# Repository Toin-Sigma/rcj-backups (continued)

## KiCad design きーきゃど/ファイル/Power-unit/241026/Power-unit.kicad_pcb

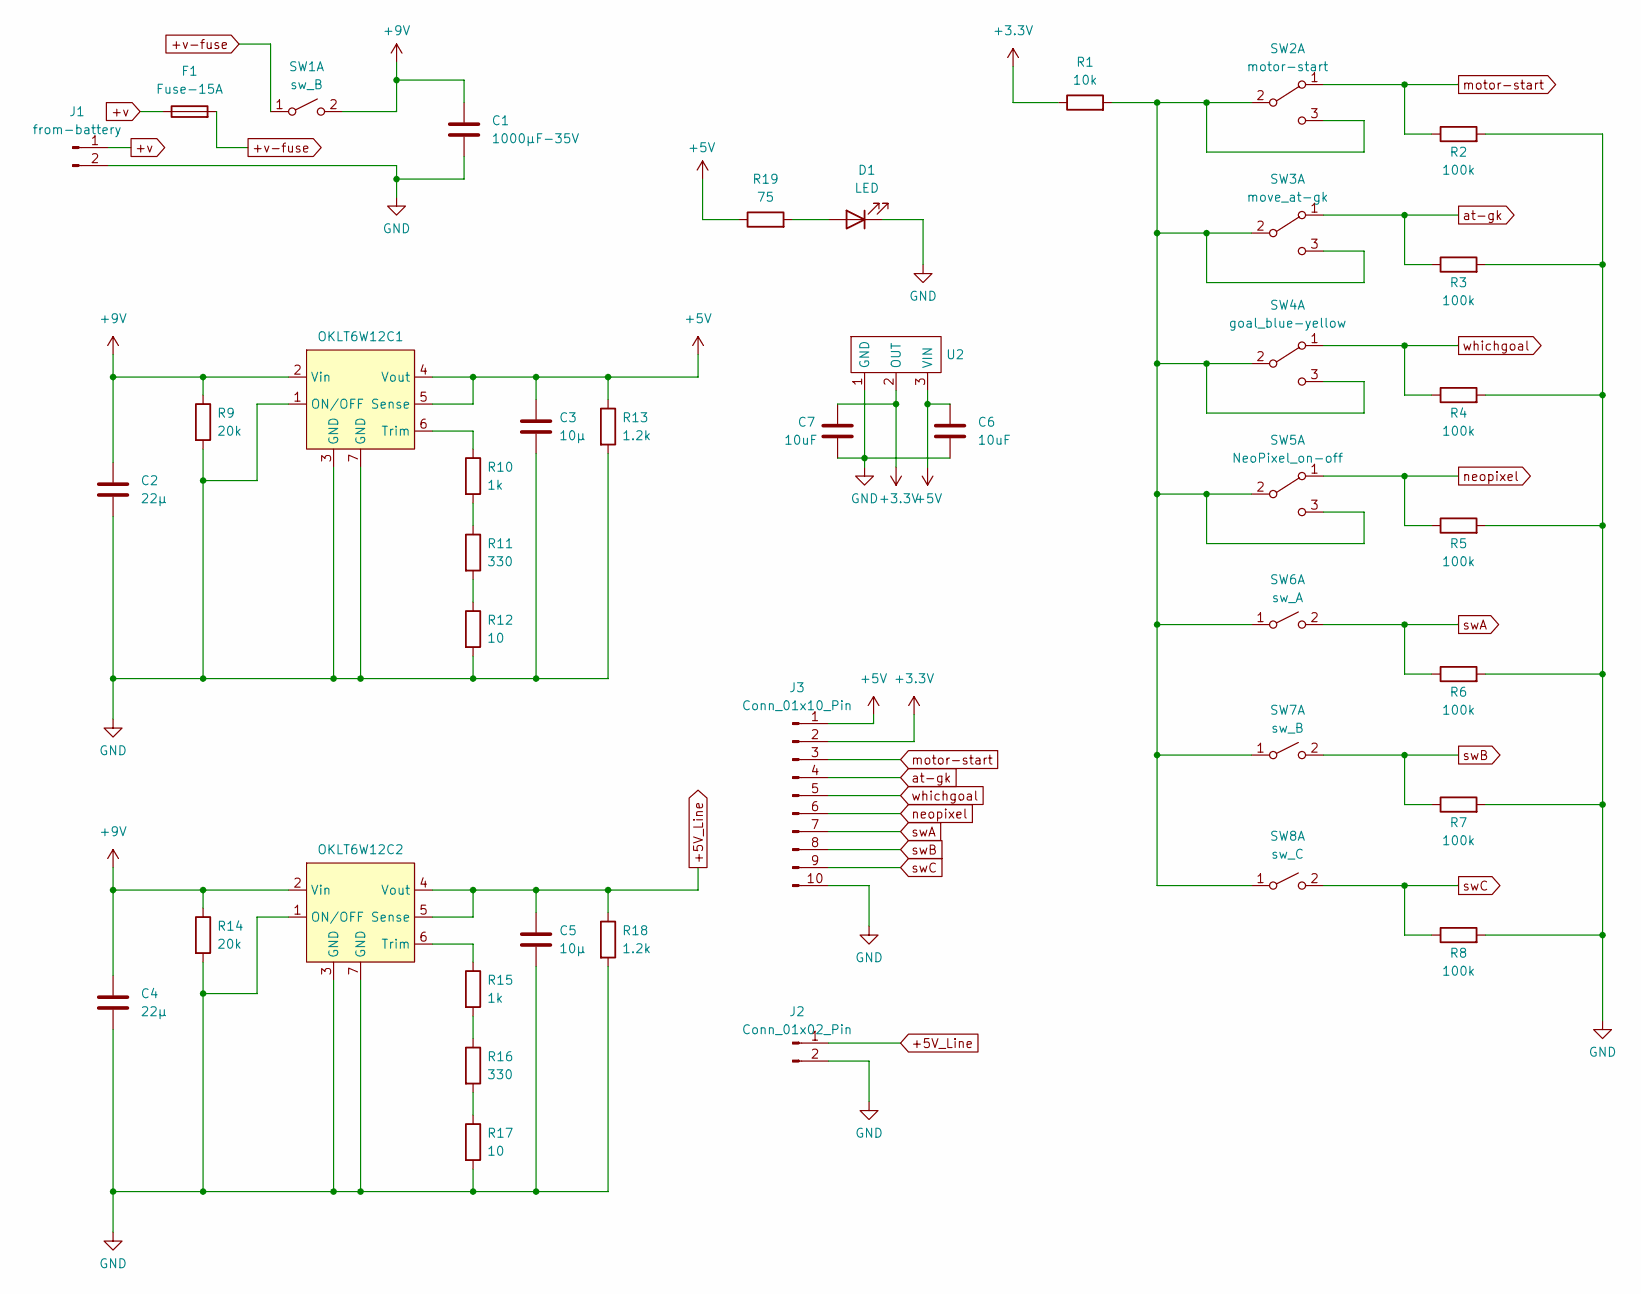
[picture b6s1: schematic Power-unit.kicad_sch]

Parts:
C1: 1000μF-35V; CP_Radial_D12.5mm_P5.00mm
C2, C4: 22μ; C_0805_2012Metric_Pad1.18x1.45mm_HandSolder
C3, C5: 10μ; C_0805_2012Metric_Pad1.18x1.45mm_HandSolder
C6, C7: 10uF; C_0805_2012Metric_Pad1.18x1.45mm_HandSolder
D1: LED; LED_0603_1608Metric
F1: Fuse-15A; mini-fuse-holder
J1: from-battery; vin
J2: Conn_01x02_Pin; AMASS_XT30U-M_1x02_P5.0mm_Vertical
J3: Conn_01x10_Pin; JST_XH_B10B-XH-A_1x10_P2.50mm_Vertical
OKLT6W12C1, OKLT6W12C2: OKL-T6-W12
R1: 10k; R_1206_3216Metric_Pad1.30x1.75mm_HandSolder
R2, R3, R4, R5, R6, R7, R8: 100k; R_1206_3216Metric_Pad1.30x1.75mm_HandSolder
R9, R14: 20k; R_1206_3216Metric_Pad1.30x1.75mm_HandSolder
R10, R15: 1k; R_1206_3216Metric_Pad1.30x1.75mm_HandSolder
R11, R16: 330; R_1206_3216Metric_Pad1.30x1.75mm_HandSolder
R12, R17: 10; R_1206_3216Metric_Pad1.30x1.75mm_HandSolder
R13, R18: 1.2k; R_1206_3216Metric_Pad1.30x1.75mm_HandSolder
R19: 75; R_1206_3216Metric_Pad1.30x1.75mm_HandSolder
SW1: sw_B; 2pin
SW2: motor-start; 2MS1-T1-B4-VS2-Q-E-S
SW3: move_at-gk; 2MS1-T1-B4-VS2-Q-E-S
SW4: goal_blue-yellow; 2MS1-T1-B4-VS2-Q-E-S
SW5: NeoPixel_on-off; 2MS1-T1-B4-VS2-Q-E-S
SW6: sw_A; TVBP06-b043CW-B
SW7: sw_B; TVBP06-b043CW-B
SW8: sw_C; TVBP06-b043CW-B
U2: SOT-223-3_TabPin2

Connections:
+3.3V: C7.2, J3.2, R1.1, U2.2 (OUT); also elsewhere on the board
+5V: C3.1, C6.1, J3.1, OKLT6W12C1.4 (Vout), OKLT6W12C1.5 (Sense), R13.1, R19.1, U2.3 (VIN); also elsewhere on the board
+5V_Line: C5.1, J2.1, OKLT6W12C2.4 (Vout), OKLT6W12C2.5 (Sense), R18.1
+9V: C1.1, C2.1, C4.1, OKLT6W12C1.2 (Vin), OKLT6W12C2.2 (Vin), R9.1, R14.1, SW1.2 (B)
+v: F1.1, J1.1
+v-fuse: F1.2, SW1.1 (A)
GND: C1.2, C2.2, C3.2, C4.2, C5.2, C6.2, C7.1, D1.1 (K), J1.2, J2.2, J3.10, OKLT6W12C1.1 (ON/OFF), OKLT6W12C1.3 (GND), OKLT6W12C1.7 (GND), OKLT6W12C2.1 (ON/OFF), OKLT6W12C2.3 (GND), OKLT6W12C2.7 (GND), R2.2, R3.2, R4.2, R5.2, R6.2, R7.2, R8.2, R9.2, R12.2, R13.2, R14.2, R17.2, R18.2, U2.1 (GND); also elsewhere on the board
unnamed 7: D1.2 (A), R19.2; also elsewhere on the board
unnamed: OKLT6W12C1.6 (Trim), R10.1
unnamed: OKLT6W12C2.6 (Trim), R15.1
unnamed: R10.2, R11.1
unnamed: R11.2, R12.1
unnamed: R15.2, R16.1
unnamed: R16.2, R17.1
unnamed: R1.2, SW2.2 (B), SW2.3 (C), SW3.2 (B), SW3.3 (C), SW4.2 (B), SW4.3 (C), SW5.2 (B), SW5.3 (C), SW6.1 (A), SW7.1 (A), SW8.1 (A)
at-gk: J3.4, R3.1, SW3.1 (A)
motor-start: J3.3, R2.1, SW2.1 (A)
neopixel: J3.6, R5.1, SW5.1 (A)
swA: J3.7, R6.1, SW6.2 (B)
swB: J3.8, R7.1, SW7.2 (B)
swC: J3.9, R8.1, SW8.2 (B)
whichgoal: J3.5, R4.1, SW4.1 (A)

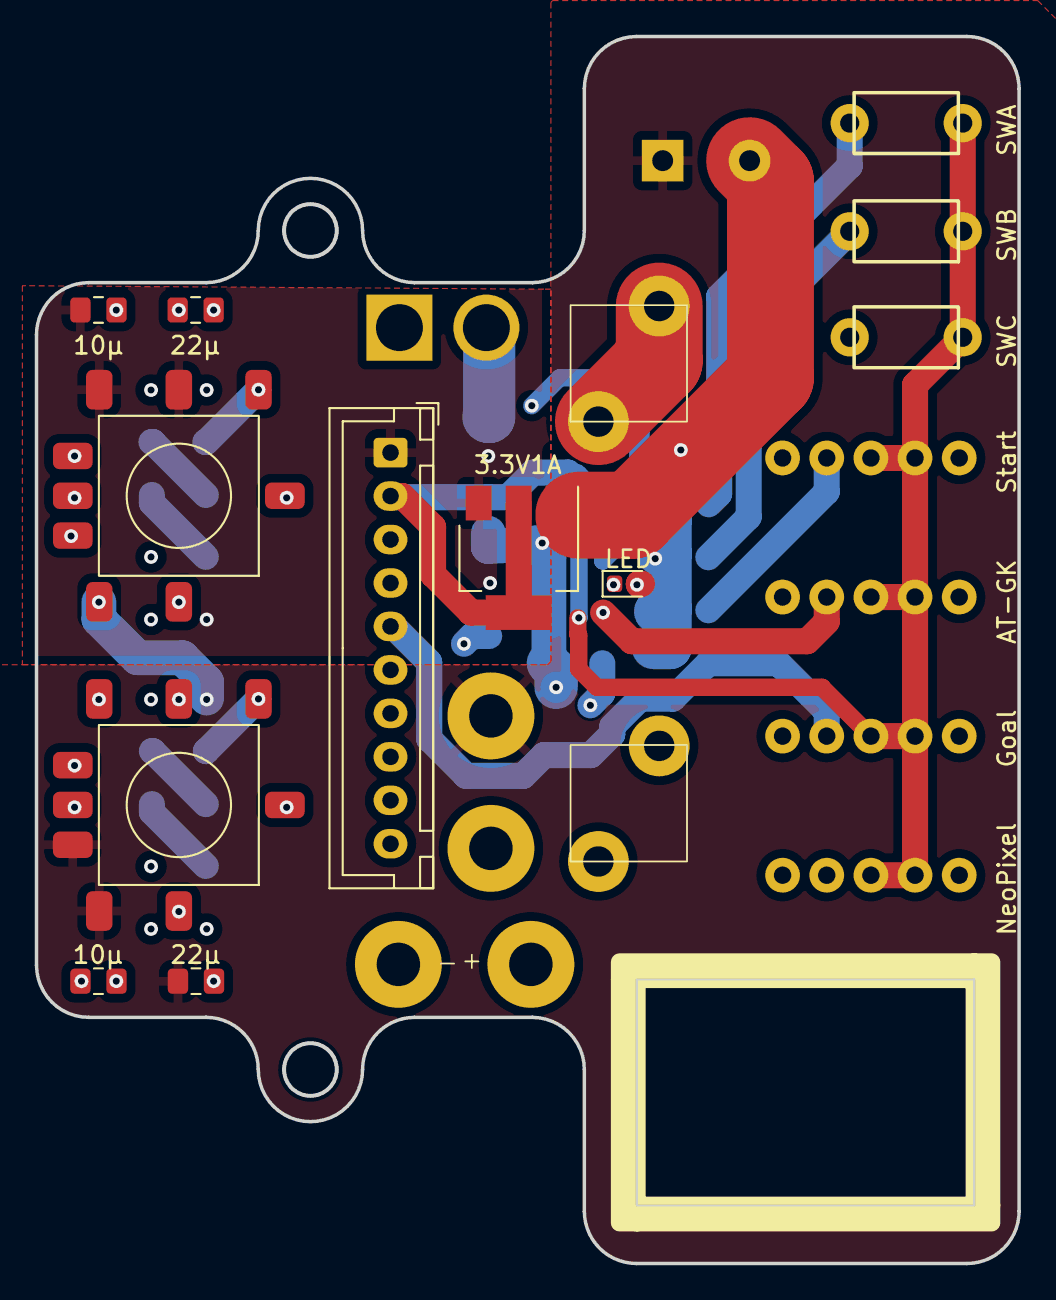
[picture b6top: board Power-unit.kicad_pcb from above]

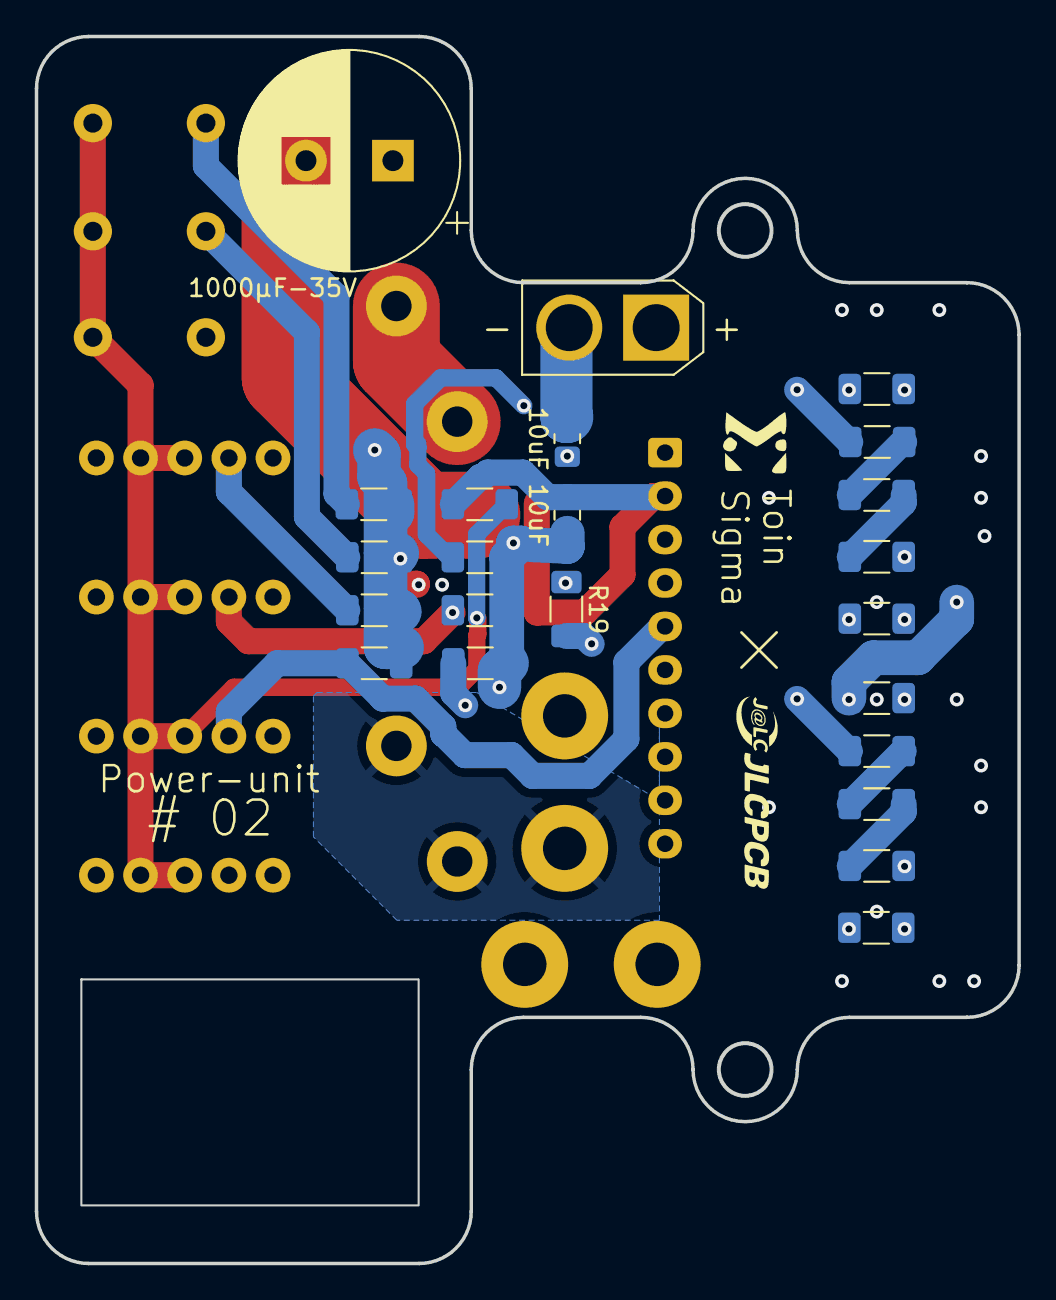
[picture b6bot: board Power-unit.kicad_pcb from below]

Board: 4 copper layers, 56.5 x 70.6 mm, 42 parts (23 on the bottom side), 22 nets.

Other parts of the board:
3.3V1A: SOT-223-3_TabPin2
10uF, 10uF#2: 10uF; C_0805_2012Metric_Pad1.18x1.45mm_HandSolder
LED: LED; LED_0603_1608Metric

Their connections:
+3.3V: 3.3V1A.2 (OUT), 10uF.2; also elsewhere on the board
+5V: 3.3V1A.3 (VIN), 10uF#2.1; also elsewhere on the board
GND: 3.3V1A.1 (GND), 10uF.1, 10uF#2.2, LED.1 (K); also elsewhere on the board
unnamed 7: LED.2 (A); also elsewhere on the board

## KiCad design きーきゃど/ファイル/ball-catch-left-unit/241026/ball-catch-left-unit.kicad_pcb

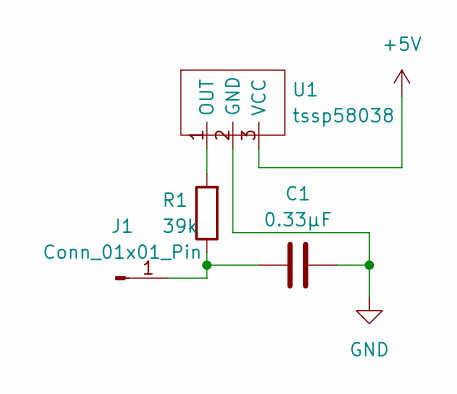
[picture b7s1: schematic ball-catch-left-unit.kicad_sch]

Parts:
C1: 0.33μF; C_0603_1608Metric_Pad1.08x0.95mm_HandSolder
J1: Conn_01x01_Pin; 1-pin
R1: 39k; R_0603_1608Metric_Pad0.98x0.95mm_HandSolder
U1: tssp58038

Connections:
+5V: U1.3 (VCC)
GND: C1.2, U1.2 (GND)
unnamed: C1.1, J1.1, R1.1
unnamed: R1.2, U1.1 (OUT)

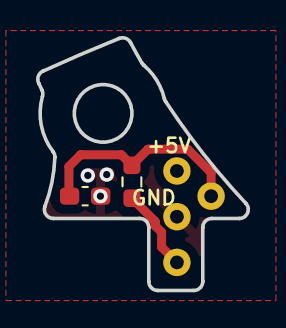
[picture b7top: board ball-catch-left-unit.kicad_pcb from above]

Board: 2 copper layers, 11.7 x 14.0 mm, 4 parts (1 on the bottom side), 3 nets.

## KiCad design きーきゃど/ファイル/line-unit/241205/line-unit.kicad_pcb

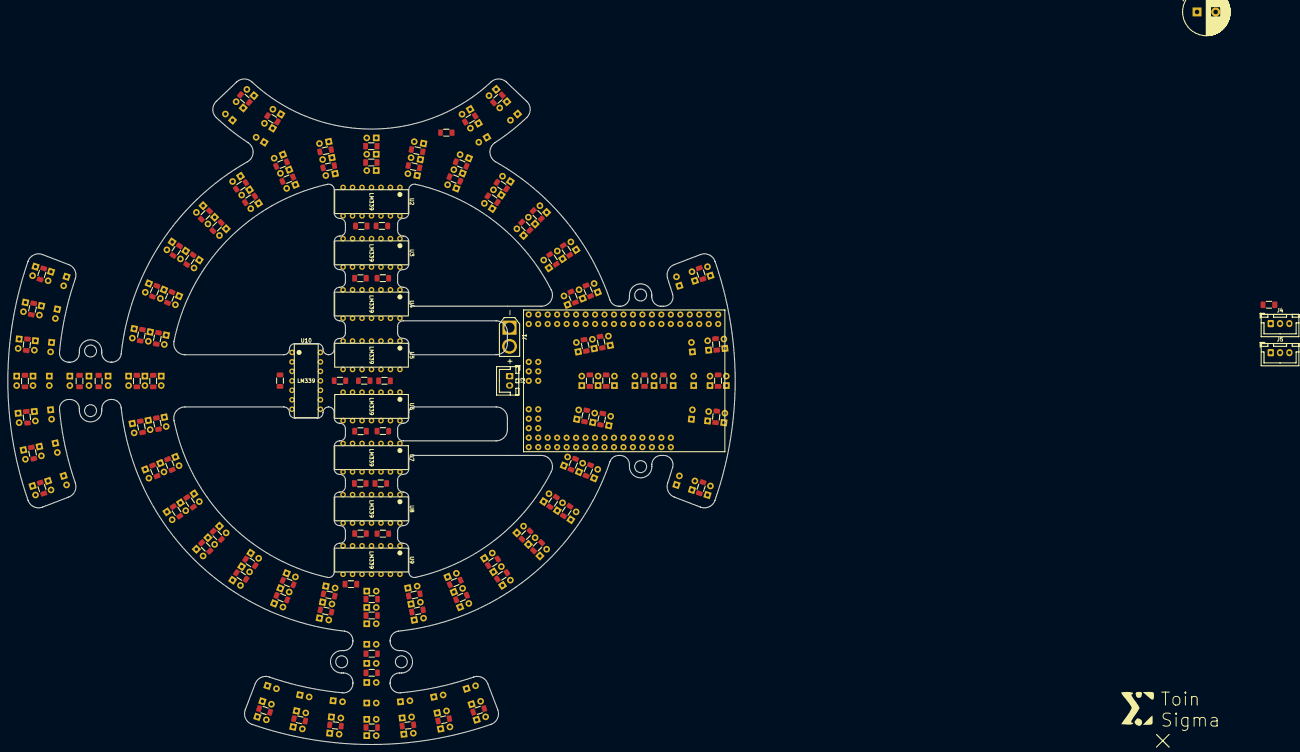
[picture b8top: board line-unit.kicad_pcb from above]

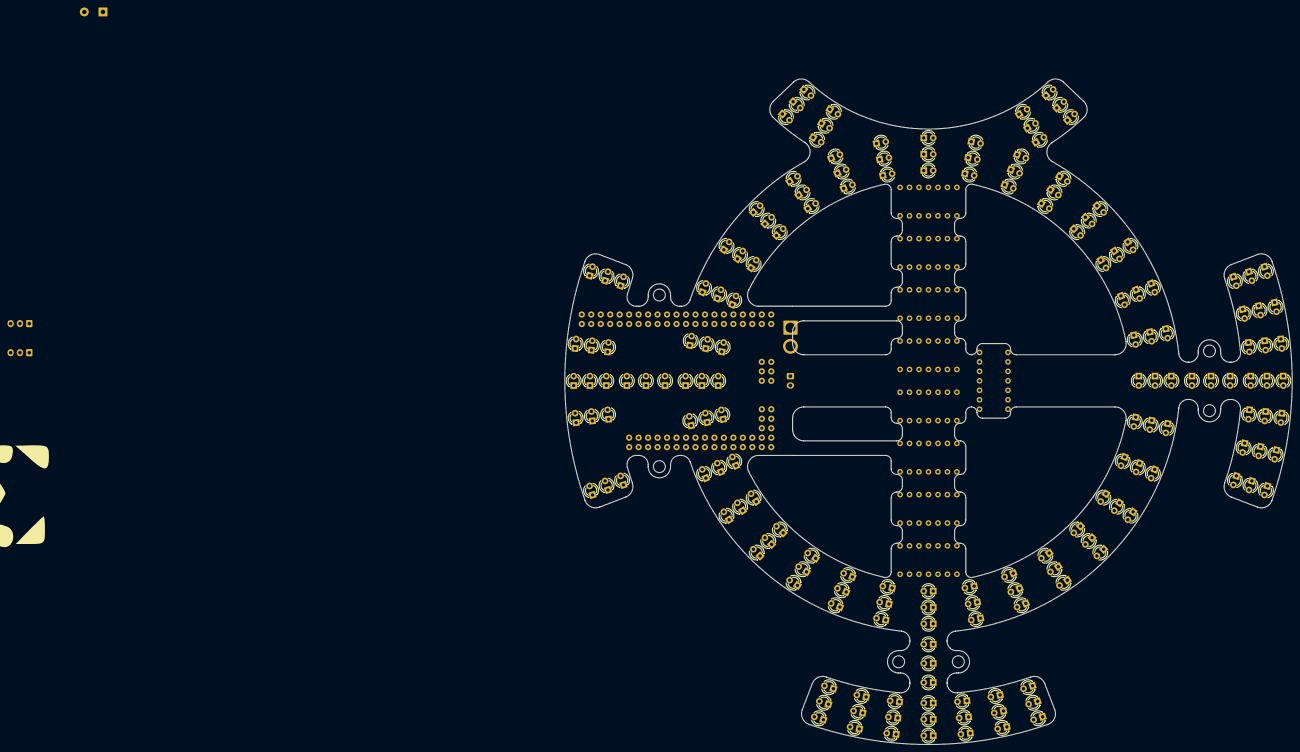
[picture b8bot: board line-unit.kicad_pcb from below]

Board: 4 copper layers, 195.0 x 178.4 mm, 299 parts (174 on the bottom side), 153 nets, no tracks yet.

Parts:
C1: 1000uF; CP_Radial_D12.5mm_P5.00mm
C2, C3, C4, C5, C6, C7, C8, C9: 10uF; C-1206_3216-Handsolder
D1, D2, D3, D4, D5, D6, D7, D8, D9, D10, D11, D12, D13, D14, D15, D16, D17, D18, D19, D20, D21, D22, D23, D24, D25, D26, D27, D28, D29, D30, D31, D32, D33, D34, D35, D36, D37, D38, D39, D40, D41, D42, D43, D44, D45, D46, D47, D48, D49, D50, D51, D52, D53, D54, D55, D56, D57, D58: LED
J1: Conn_01x02_Pin; AMASS_XT30U-F_1x02_P5.0mm_Vertical
J2: Conn_01x02_Pin; JST_XH_B2B-XH-A_1x02_P2.50mm_Vertical
J4, J5: Conn_01x03_Pin; JST_XH_B3B-XH-A_1x03_P2.50mm_Vertical
NJL7502L1, NJL7502L2, NJL7502L3, NJL7502L4, NJL7502L5, NJL7502L6, NJL7502L7, NJL7502L8, NJL7502L9, NJL7502L10, NJL7502L11, NJL7502L12, NJL7502L13, NJL7502L14, NJL7502L15, NJL7502L16, NJL7502L17, NJL7502L18, NJL7502L19, NJL7502L20, NJL7502L21, NJL7502L22, NJL7502L23, NJL7502L24, NJL7502L25, NJL7502L26, NJL7502L27, NJL7502L28, NJL7502L29, NJL7502L30, NJL7502L31, NJL7502L32, NJL7502L33, NJL7502L34, NJL7502L35, NJL7502L36, NJL7502L37, NJL7502L38, NJL7502L39, NJL7502L40, NJL7502L41, NJL7502L42, NJL7502L43, NJL7502L44, NJL7502L45, NJL7502L46, NJL7502L47, NJL7502L48, NJL7502L49, NJL7502L50, NJL7502L51, NJL7502L52, NJL7502L53, NJL7502L54, NJL7502L55, NJL7502L56, NJL7502L57, NJL7502L58, NJL7502L59, NJL7502L60, NJL7502L61, NJL7502L62, NJL7502L63, NJL7502L64, NJL7502L65, NJL7502L66, NJL7502L67, NJL7502L68, NJL7502L69, NJL7502L70, NJL7502L71, NJL7502L72, NJL7502L73, NJL7502L74, NJL7502L75, NJL7502L76, NJL7502L77, NJL7502L78, NJL7502L79, NJL7502L80, NJL7502L81, NJL7502L82, NJL7502L83, NJL7502L84, NJL7502L85, NJL7502L86, NJL7502L87, NJL7502L88, NJL7502L89, NJL7502L90, NJL7502L91, NJL7502L92, NJL7502L93, NJL7502L94, NJL7502L95, NJL7502L96, NJL7502L97, NJL7502L98, NJL7502L99, NJL7502L100, NJL7502L101, NJL7502L102, NJL7502L103, NJL7502L104, NJL7502L105, NJL7502L106, NJL7502L107, NJL7502L108, NJL7502L109, NJL7502L110, NJL7502L111, NJL7502L112, NJL7502L113, NJL7502L114, NJL7502L115, NJL7502L116: NJL7502L
R1, R2, R3, R4, R5, R6, R7, R8, R9, R10, R11, R12, R13, R14, R15, R16, R17, R18, R19, R20, R21, R22, R23, R24, R25, R26, R27, R28, R29, R30, R31, R32, R65, R66, R67, R68, R69, R70, R71, R72, R73, R74, R75, R76, R77, R78, R79, R80, R81, R82, R83, R84, R85, R86, R87, R88, R89, R90: 75; R-1206_3216-Handsolder
R33, R34, R35, R36, R37, R38, R39, R40, R41, R42, R43, R44, R45, R46, R47, R48, R49, R50, R51, R52, R53, R54, R55, R56, R57, R58, R59, R60, R61, R62, R63, R64, R91, R92, R93, R94: 10k; R-1206_3216-Handsolder
R95, R96, R97, R98, R99, R100, R101, R102: 1k; R-1206_3216-Handsolder
U1: MEGA_PRO_EMBED_CH340G_{slash}_ATMEGA2560; MODULE_MEGA_PRO_EMBED_CH340G___ATMEGA2560
U2, U3, U4, U5, U6, U7, U8, U9, U10: LM339

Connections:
+5V: C1.1, J1.1, J4.1, J5.1, NJL7502L1.2 (Collector), NJL7502L2.2 (Collector), NJL7502L3.2 (Collector), NJL7502L4.2 (Collector), NJL7502L5.2 (Collector), NJL7502L6.2 (Collector), NJL7502L7.2 (Collector), NJL7502L8.2 (Collector), NJL7502L9.2 (Collector), NJL7502L10.2 (Collector), NJL7502L11.2 (Collector), NJL7502L12.2 (Collector), NJL7502L13.2 (Collector), NJL7502L14.2 (Collector), NJL7502L15.2 (Collector), NJL7502L16.2 (Collector), NJL7502L17.2 (Collector), NJL7502L18.2 (Collector), NJL7502L19.2 (Collector), NJL7502L20.2 (Collector), NJL7502L21.2 (Collector), NJL7502L22.2 (Collector), NJL7502L23.2 (Collector), NJL7502L24.2 (Collector), NJL7502L25.2 (Collector), NJL7502L26.2 (Collector), NJL7502L27.2 (Collector), NJL7502L28.2 (Collector), NJL7502L29.2 (Collector), NJL7502L30.2 (Collector), NJL7502L31.2 (Collector), NJL7502L32.2 (Collector), NJL7502L33.2 (Collector), NJL7502L34.2 (Collector), NJL7502L35.2 (Collector), NJL7502L36.2 (Collector), NJL7502L37.2 (Collector), NJL7502L38.2 (Collector), NJL7502L39.2 (Collector), NJL7502L40.2 (Collector), NJL7502L41.2 (Collector), NJL7502L42.2 (Collector), NJL7502L43.2 (Collector), NJL7502L44.2 (Collector), NJL7502L45.2 (Collector), NJL7502L46.2 (Collector), NJL7502L47.2 (Collector), NJL7502L48.2 (Collector), NJL7502L49.2 (Collector), NJL7502L50.2 (Collector), NJL7502L51.2 (Collector), NJL7502L52.2 (Collector), NJL7502L53.2 (Collector), NJL7502L54.2 (Collector), NJL7502L55.2 (Collector), NJL7502L56.2 (Collector), NJL7502L57.2 (Collector), NJL7502L58.2 (Collector), NJL7502L59.2 (Collector), NJL7502L60.2 (Collector), NJL7502L61.2 (Collector), NJL7502L62.2 (Collector), NJL7502L63.2 (Collector), NJL7502L64.2 (Collector), NJL7502L65.2 (Collector), NJL7502L66.2 (Collector), NJL7502L67.2 (Collector), NJL7502L68.2 (Collector), NJL7502L69.2 (Collector), NJL7502L70.2 (Collector), NJL7502L71.2 (Collector), NJL7502L72.2 (Collector), NJL7502L73.2 (Collector), NJL7502L74.2 (Collector), NJL7502L75.2 (Collector), NJL7502L76.2 (Collector), NJL7502L77.2 (Collector), NJL7502L78.2 (Collector), NJL7502L79.2 (Collector), NJL7502L80.2 (Collector), NJL7502L81.2 (Collector), NJL7502L82.2 (Collector), NJL7502L83.2 (Collector), NJL7502L84.2 (Collector), NJL7502L85.2 (Collector), NJL7502L86.2 (Collector), NJL7502L87.2 (Collector), NJL7502L88.2 (Collector), NJL7502L89.2 (Collector), NJL7502L90.2 (Collector), NJL7502L91.2 (Collector), NJL7502L92.2 (Collector), NJL7502L93.2 (Collector), NJL7502L94.2 (Collector), NJL7502L95.2 (Collector), NJL7502L96.2 (Collector), NJL7502L97.2 (Collector), NJL7502L98.2 (Collector), NJL7502L99.2 (Collector), NJL7502L100.2 (Collector), NJL7502L101.2 (Collector), NJL7502L102.2 (Collector), NJL7502L103.2 (Collector), NJL7502L104.2 (Collector), NJL7502L105.2 (Collector), NJL7502L106.2 (Collector), NJL7502L107.2 (Collector), NJL7502L108.2 (Collector), NJL7502L109.2 (Collector), NJL7502L110.2 (Collector), NJL7502L111.2 (Collector), NJL7502L112.2 (Collector), NJL7502L113.2 (Collector), NJL7502L114.2 (Collector), NJL7502L115.2 (Collector), NJL7502L116.2 (Collector), R1.2, R2.2, R3.2, R4.2, R5.2, R6.2, R7.2, R8.2, R9.2, R10.2, R11.2, R12.2, R13.2, R14.2, R15.2, R16.2, R17.2, R18.2, R19.2, R20.2, R21.2, R22.2, R23.2, R24.2, R25.2, R26.2, R27.2, R28.2, R29.2, R30.2, R31.2, R32.2, R65.2, R66.2, R67.2, R68.2, R69.2, R70.2, R71.2, R72.2, R73.2, R74.2, R75.2, R76.2, R77.2, R78.2, R79.2, R80.2, R81.2, R82.2, R83.2, R84.2, R85.2, R86.2, R87.2, R88.2, R89.2, R90.2, U1.VIN_1 (VIN), U1.VIN_2 (VIN), U2.3 (VCC), U3.3 (VCC), U4.3 (VCC), U5.3 (VCC), U6.3 (VCC), U7.3 (VCC), U8.3 (VCC), U9.3 (VCC), U10.3 (VCC)
GND: C1.2, C2.2, C3.2, C4.2, C5.2, C6.2, C7.2, C8.2, C9.2, D1.1 (K), D2.1 (K), D3.1 (K), D4.1 (K), D5.1 (K), D6.1 (K), D7.1 (K), D8.1 (K), D9.1 (K), D10.1 (K), D11.1 (K), D12.1 (K), D13.1 (K), D14.1 (K), D15.1 (K), D16.1 (K), D17.1 (K), D18.1 (K), D19.1 (K), D20.1 (K), D21.1 (K), D22.1 (K), D23.1 (K), D24.1 (K), D25.1 (K), D26.1 (K), D27.1 (K), D28.1 (K), D29.1 (K), D30.1 (K), D31.1 (K), D32.1 (K), D33.1 (K), D34.1 (K), D35.1 (K), D36.1 (K), D37.1 (K), D38.1 (K), D39.1 (K), D40.1 (K), D41.1 (K), D42.1 (K), D43.1 (K), D44.1 (K), D45.1 (K), D46.1 (K), D47.1 (K), D48.1 (K), D49.1 (K), D50.1 (K), D51.1 (K), D52.1 (K), D53.1 (K), D54.1 (K), D55.1 (K), D56.1 (K), D57.1 (K), D58.1 (K), J1.2, J4.3, J5.3, R33.1, R34.1, R35.1, R36.1, R37.1, R38.1, R39.1, R40.1, R41.1, R42.1, R43.1, R44.1, R45.1, R46.1, R47.1, R48.1, R49.1, R50.1, R51.1, R52.1, R53.1, R54.1, R55.1, R56.1, R57.1, R58.1, R59.1, R60.1, R61.1, R62.1, R63.1, R64.1, R91.1, R92.1, R93.1, R94.1, U1.GND_1 (GND), U1.GND_2 (GND), U1.GND_3 (GND), U2.12 (GND), U3.12 (GND), U4.12 (GND), U5.12 (GND), U6.12 (GND), U7.12 (GND), U8.12 (GND), U9.12 (GND), U10.12 (GND)
unnamed: D1.2 (A), R1.1
unnamed: D2.2 (A), R2.1
unnamed: D3.2 (A), R3.1
unnamed: D4.2 (A), R4.1
unnamed: D5.2 (A), R5.1
unnamed: D6.2 (A), R6.1
unnamed: D7.2 (A), R7.1
unnamed: D8.2 (A), R8.1
unnamed: D9.2 (A), R9.1
unnamed: D10.2 (A), R10.1
unnamed: D11.2 (A), R11.1
unnamed: D12.2 (A), R12.1
unnamed: D13.2 (A), R13.1
unnamed: D14.2 (A), R14.1
unnamed: D15.2 (A), R15.1
unnamed: D16.2 (A), R16.1
unnamed: D17.2 (A), R17.1
unnamed: D18.2 (A), R18.1
unnamed: D19.2 (A), R19.1
unnamed: D20.2 (A), R20.1
unnamed: D21.2 (A), R21.1
unnamed: D22.2 (A), R22.1
unnamed: D23.2 (A), R23.1
unnamed: D24.2 (A), R24.1
unnamed: D25.2 (A), R25.1
unnamed: D26.2 (A), R26.1
unnamed: D27.2 (A), R27.1
unnamed: D28.2 (A), R28.1
unnamed: D29.2 (A), R29.1
unnamed: D30.2 (A), R30.1
unnamed: D31.2 (A), R31.1
unnamed: D32.2 (A), R32.1
unnamed: D33.2 (A), R65.1
unnamed: D34.2 (A), R66.1
unnamed: D35.2 (A), R67.1
unnamed: D36.2 (A), R68.1
unnamed: D37.2 (A), R69.1
unnamed: D38.2 (A), R70.1
unnamed: D39.2 (A), R71.1
unnamed: D40.2 (A), R72.1
unnamed: D41.2 (A), R73.1
unnamed: D42.2 (A), R74.1
unnamed: D43.2 (A), R75.1
unnamed: D44.2 (A), R76.1
unnamed: D45.2 (A), R77.1
unnamed: D46.2 (A), R78.1
unnamed: D47.2 (A), R79.1
unnamed: D48.2 (A), R80.1
unnamed: D49.2 (A), R81.1
unnamed: D50.2 (A), R82.1
unnamed: D51.2 (A), R83.1
unnamed: D52.2 (A), R84.1
unnamed: D53.2 (A), R85.1
unnamed: D54.2 (A), R86.1
unnamed: D55.2 (A), R87.1
unnamed: D56.2 (A), R88.1
unnamed: D57.2 (A), R89.1
unnamed: D58.2 (A), R90.1
RX_5V: J2.2, U1.D19
TX_5V: J2.1, U1.D18
ballcatch_left: J5.2, U1.A1
ballcatch_right: J4.2, U1.A0
boundary1: C2.1, R95.2, U2.4 (2IN-), U2.6 (1IN-), U2.8 (3IN-), U2.10 (4IN-)
boundary1_raw: R95.1, U1.D2
boundary2: C3.1, R96.2, U3.4 (2IN-), U3.6 (1IN-), U4.4 (2IN-), U4.6 (1IN-)
boundary2_raw: R96.1, U1.D3
boundary3: C4.1, R97.2, U5.4 (2IN-), U5.6 (1IN-), U6.4 (2IN-), U6.10 (4IN-)
boundary3_raw: R97.1, U1.D4
boundary4: C5.1, R98.2, U6.6 (1IN-), U6.8 (3IN-), U7.4 (2IN-), U7.6 (1IN-)
boundary4_raw: R98.1, U1.D5
boundary5: C6.1, R99.2, U8.4 (2IN-), U8.6 (1IN-), U9.4 (2IN-), U9.6 (1IN-)
boundary5_raw: R99.1, U1.D6
boundary6: C7.1, R100.2, U8.8 (3IN-), U8.10 (4IN-), U9.8 (3IN-), U9.10 (4IN-)
boundary6_raw: R100.1, U1.D7
boundary7: C8.1, R101.2, U7.8 (3IN-), U7.10 (4IN-), U10.4 (2IN-), U10.6 (1IN-)
boundary7_raw: R101.1, U1.D8
boundary8: C9.1, R102.2, U5.8 (3IN-), U5.10 (4IN-), U10.8 (3IN-), U10.10 (4IN-)
boundary8_raw: R102.1, U1.D9
boundary9: U3.8 (3IN-), U3.10 (4IN-), U4.8 (3IN-), U4.10 (4IN-)
linesig1: U1.D11, U2.1 (1OUT)
linesig2: U1.D12, U2.2 (2OUT)
linesig3: U1.D13, U3.1 (1OUT)
linesig4: U1.D14, U3.2 (2OUT)
linesig5: U1.D15, U4.1 (1OUT)
linesig6: U1.D16, U4.2 (2OUT)
linesig7: U1.D17, U5.1 (1OUT)
linesig8: U1.D22, U5.2 (2OUT)
linesig9: U1.D23, U6.2 (2OUT)
linesig10: U1.D24, U6.1 (1OUT)
linesig11: U1.D25, U6.14 (3OUT)
linesig12: U1.D26, U7.1 (1OUT)
linesig13: U1.D27, U7.2 (2OUT)
linesig14: U1.D28, U8.1 (1OUT)
linesig15: U1.D29, U8.2 (2OUT)
linesig16: U1.D30, U9.1 (1OUT)
linesig17: U1.D31, U9.2 (2OUT)
linesig18: U1.D32, U9.14 (3OUT)
linesig19: U1.D33, U8.14 (3OUT)
linesig20: U1.D34, U8.13 (4OUT)
linesig21: U1.D35, U7.14 (3OUT)
linesig22: U1.D36, U7.13 (4OUT)
linesig23: U1.D37, U10.1 (1OUT)
linesig24: U1.D38, U10.2 (2OUT)
linesig25: U1.D39, U10.14 (3OUT)
linesig26: U1.D40, U5.14 (3OUT)
linesig27: U1.D41, U5.13 (4OUT)
linesig28: U1.D42, U4.14 (3OUT)
linesig29: U1.D43, U4.13 (4OUT)
linesig30: U1.D44, U3.14 (3OUT)
linesig31: U1.D45, U3.13 (4OUT)
linesig32: U1.D46, U2.14 (3OUT)
linesig33: U1.D47, U2.13 (4OUT)
linesig34: U1.D48, U6.13 (4OUT)
linesig35: U1.D49, U9.13 (4OUT)
linesig36: U1.D50, U10.13 (4OUT)
sig1: NJL7502L1.1 (Emitter), NJL7502L2.1 (Emitter), R33.2, U2.7 (1IN+)
sig2: NJL7502L3.1 (Emitter), NJL7502L4.1 (Emitter), R34.2, U2.5 (2IN+)
sig3: NJL7502L5.1 (Emitter), NJL7502L6.1 (Emitter), R35.2, U3.7 (1IN+)
sig4: NJL7502L7.1 (Emitter), NJL7502L8.1 (Emitter), R36.2, U3.5 (2IN+)
sig5: NJL7502L9.1 (Emitter), NJL7502L10.1 (Emitter), R37.2, U4.7 (1IN+)
sig6: NJL7502L11.1 (Emitter), NJL7502L12.1 (Emitter), R38.2, U4.5 (2IN+)
sig7: NJL7502L13.1 (Emitter), NJL7502L14.1 (Emitter), R39.2, U5.7 (1IN+)
sig8: NJL7502L15.1 (Emitter), NJL7502L16.1 (Emitter), R40.2, U5.5 (2IN+)
sig9: NJL7502L17.1 (Emitter), NJL7502L18.1 (Emitter), R41.2, U6.5 (2IN+)
sig10: NJL7502L19.1 (Emitter), NJL7502L20.1 (Emitter), R42.2, U6.7 (1IN+)
sig11: NJL7502L21.1 (Emitter), NJL7502L22.1 (Emitter), R43.2, U6.9 (3IN+)
sig12: NJL7502L23.1 (Emitter), NJL7502L24.1 (Emitter), R44.2, U7.7 (1IN+)
sig13: NJL7502L25.1 (Emitter), NJL7502L26.1 (Emitter), R45.2, U7.5 (2IN+)
sig14: NJL7502L27.1 (Emitter), NJL7502L28.1 (Emitter), R46.2, U8.7 (1IN+)
sig15: NJL7502L29.1 (Emitter), NJL7502L30.1 (Emitter), R47.2, U8.5 (2IN+)
sig16: NJL7502L31.1 (Emitter), NJL7502L32.1 (Emitter), R48.2, U9.7 (1IN+)
sig17: NJL7502L33.1 (Emitter), NJL7502L34.1 (Emitter), R49.2, U9.5 (2IN+)
sig18: NJL7502L35.1 (Emitter), NJL7502L36.1 (Emitter), R50.2, U9.11 (4IN+)
sig19: NJL7502L37.1 (Emitter), NJL7502L38.1 (Emitter), R51.2, U8.9 (3IN+)
sig20: NJL7502L39.1 (Emitter), NJL7502L40.1 (Emitter), R52.2, U8.11 (4IN+)
sig21: NJL7502L41.1 (Emitter), NJL7502L42.1 (Emitter), R53.2, U7.9 (3IN+)
sig22: NJL7502L43.1 (Emitter), NJL7502L44.1 (Emitter), R54.2, U7.11 (4IN+)
sig23: NJL7502L45.1 (Emitter), NJL7502L46.1 (Emitter), R55.2, U10.7 (1IN+)
sig24: NJL7502L47.1 (Emitter), NJL7502L48.1 (Emitter), R56.2, U10.5 (2IN+)
sig25: NJL7502L49.1 (Emitter), NJL7502L50.1 (Emitter), R57.2, U10.9 (3IN+)
sig26: NJL7502L51.1 (Emitter), NJL7502L52.1 (Emitter), R58.2, U5.9 (3IN+)
sig27: NJL7502L53.1 (Emitter), NJL7502L54.1 (Emitter), R59.2, U5.11 (4IN+)
sig28: NJL7502L55.1 (Emitter), NJL7502L56.1 (Emitter), R60.2, U4.9 (3IN+)
sig29: NJL7502L57.1 (Emitter), NJL7502L58.1 (Emitter), R61.2, U4.11 (4IN+)
sig30: NJL7502L59.1 (Emitter), NJL7502L60.1 (Emitter), R62.2, U3.9 (3IN+)
sig31: NJL7502L61.1 (Emitter), NJL7502L62.1 (Emitter), R63.2, U3.11 (4IN+)
sig32: NJL7502L63.1 (Emitter), NJL7502L64.1 (Emitter), R64.2, U2.9 (3IN+)
sig33: NJL7502L65.1 (Emitter), NJL7502L66.1 (Emitter), NJL7502L67.1 (Emitter), NJL7502L68.1 (Emitter), NJL7502L69.1 (Emitter), NJL7502L70.1 (Emitter), NJL7502L71.1 (Emitter), NJL7502L72.1 (Emitter), R91.2, U2.11 (4IN+)
sig34: NJL7502L73.1 (Emitter), NJL7502L74.1 (Emitter), NJL7502L75.1 (Emitter), NJL7502L76.1 (Emitter), NJL7502L77.1 (Emitter), NJL7502L78.1 (Emitter), NJL7502L79.1 (Emitter), NJL7502L80.1 (Emitter), NJL7502L81.1 (Emitter), NJL7502L82.1 (Emitter), NJL7502L83.1 (Emitter), NJL7502L84.1 (Emitter), R92.2, U6.11 (4IN+)
sig35: NJL7502L85.1 (Emitter), NJL7502L86.1 (Emitter), NJL7502L87.1 (Emitter), NJL7502L88.1 (Emitter), NJL7502L89.1 (Emitter), NJL7502L90.1 (Emitter), NJL7502L91.1 (Emitter), NJL7502L92.1 (Emitter), NJL7502L93.1 (Emitter), NJL7502L94.1 (Emitter), NJL7502L95.1 (Emitter), NJL7502L96.1 (Emitter), NJL7502L97.1 (Emitter), NJL7502L98.1 (Emitter), NJL7502L99.1 (Emitter), NJL7502L100.1 (Emitter), R93.2, U9.9 (3IN+)
sig36: NJL7502L101.1 (Emitter), NJL7502L102.1 (Emitter), NJL7502L103.1 (Emitter), NJL7502L104.1 (Emitter), NJL7502L105.1 (Emitter), NJL7502L106.1 (Emitter), NJL7502L107.1 (Emitter), NJL7502L108.1 (Emitter), NJL7502L109.1 (Emitter), NJL7502L110.1 (Emitter), NJL7502L111.1 (Emitter), NJL7502L112.1 (Emitter), NJL7502L113.1 (Emitter), NJL7502L114.1 (Emitter), NJL7502L115.1 (Emitter), NJL7502L116.1 (Emitter), R94.2, U10.11 (4IN+)
